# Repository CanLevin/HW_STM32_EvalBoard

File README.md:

# HW_STM32_EvalBoard
# HW Circuit and Layout for a simple Evaluation Board for a STM32F401
# wtih:
# SPI
# I2C
# UART
# USART# USB_HS-FS

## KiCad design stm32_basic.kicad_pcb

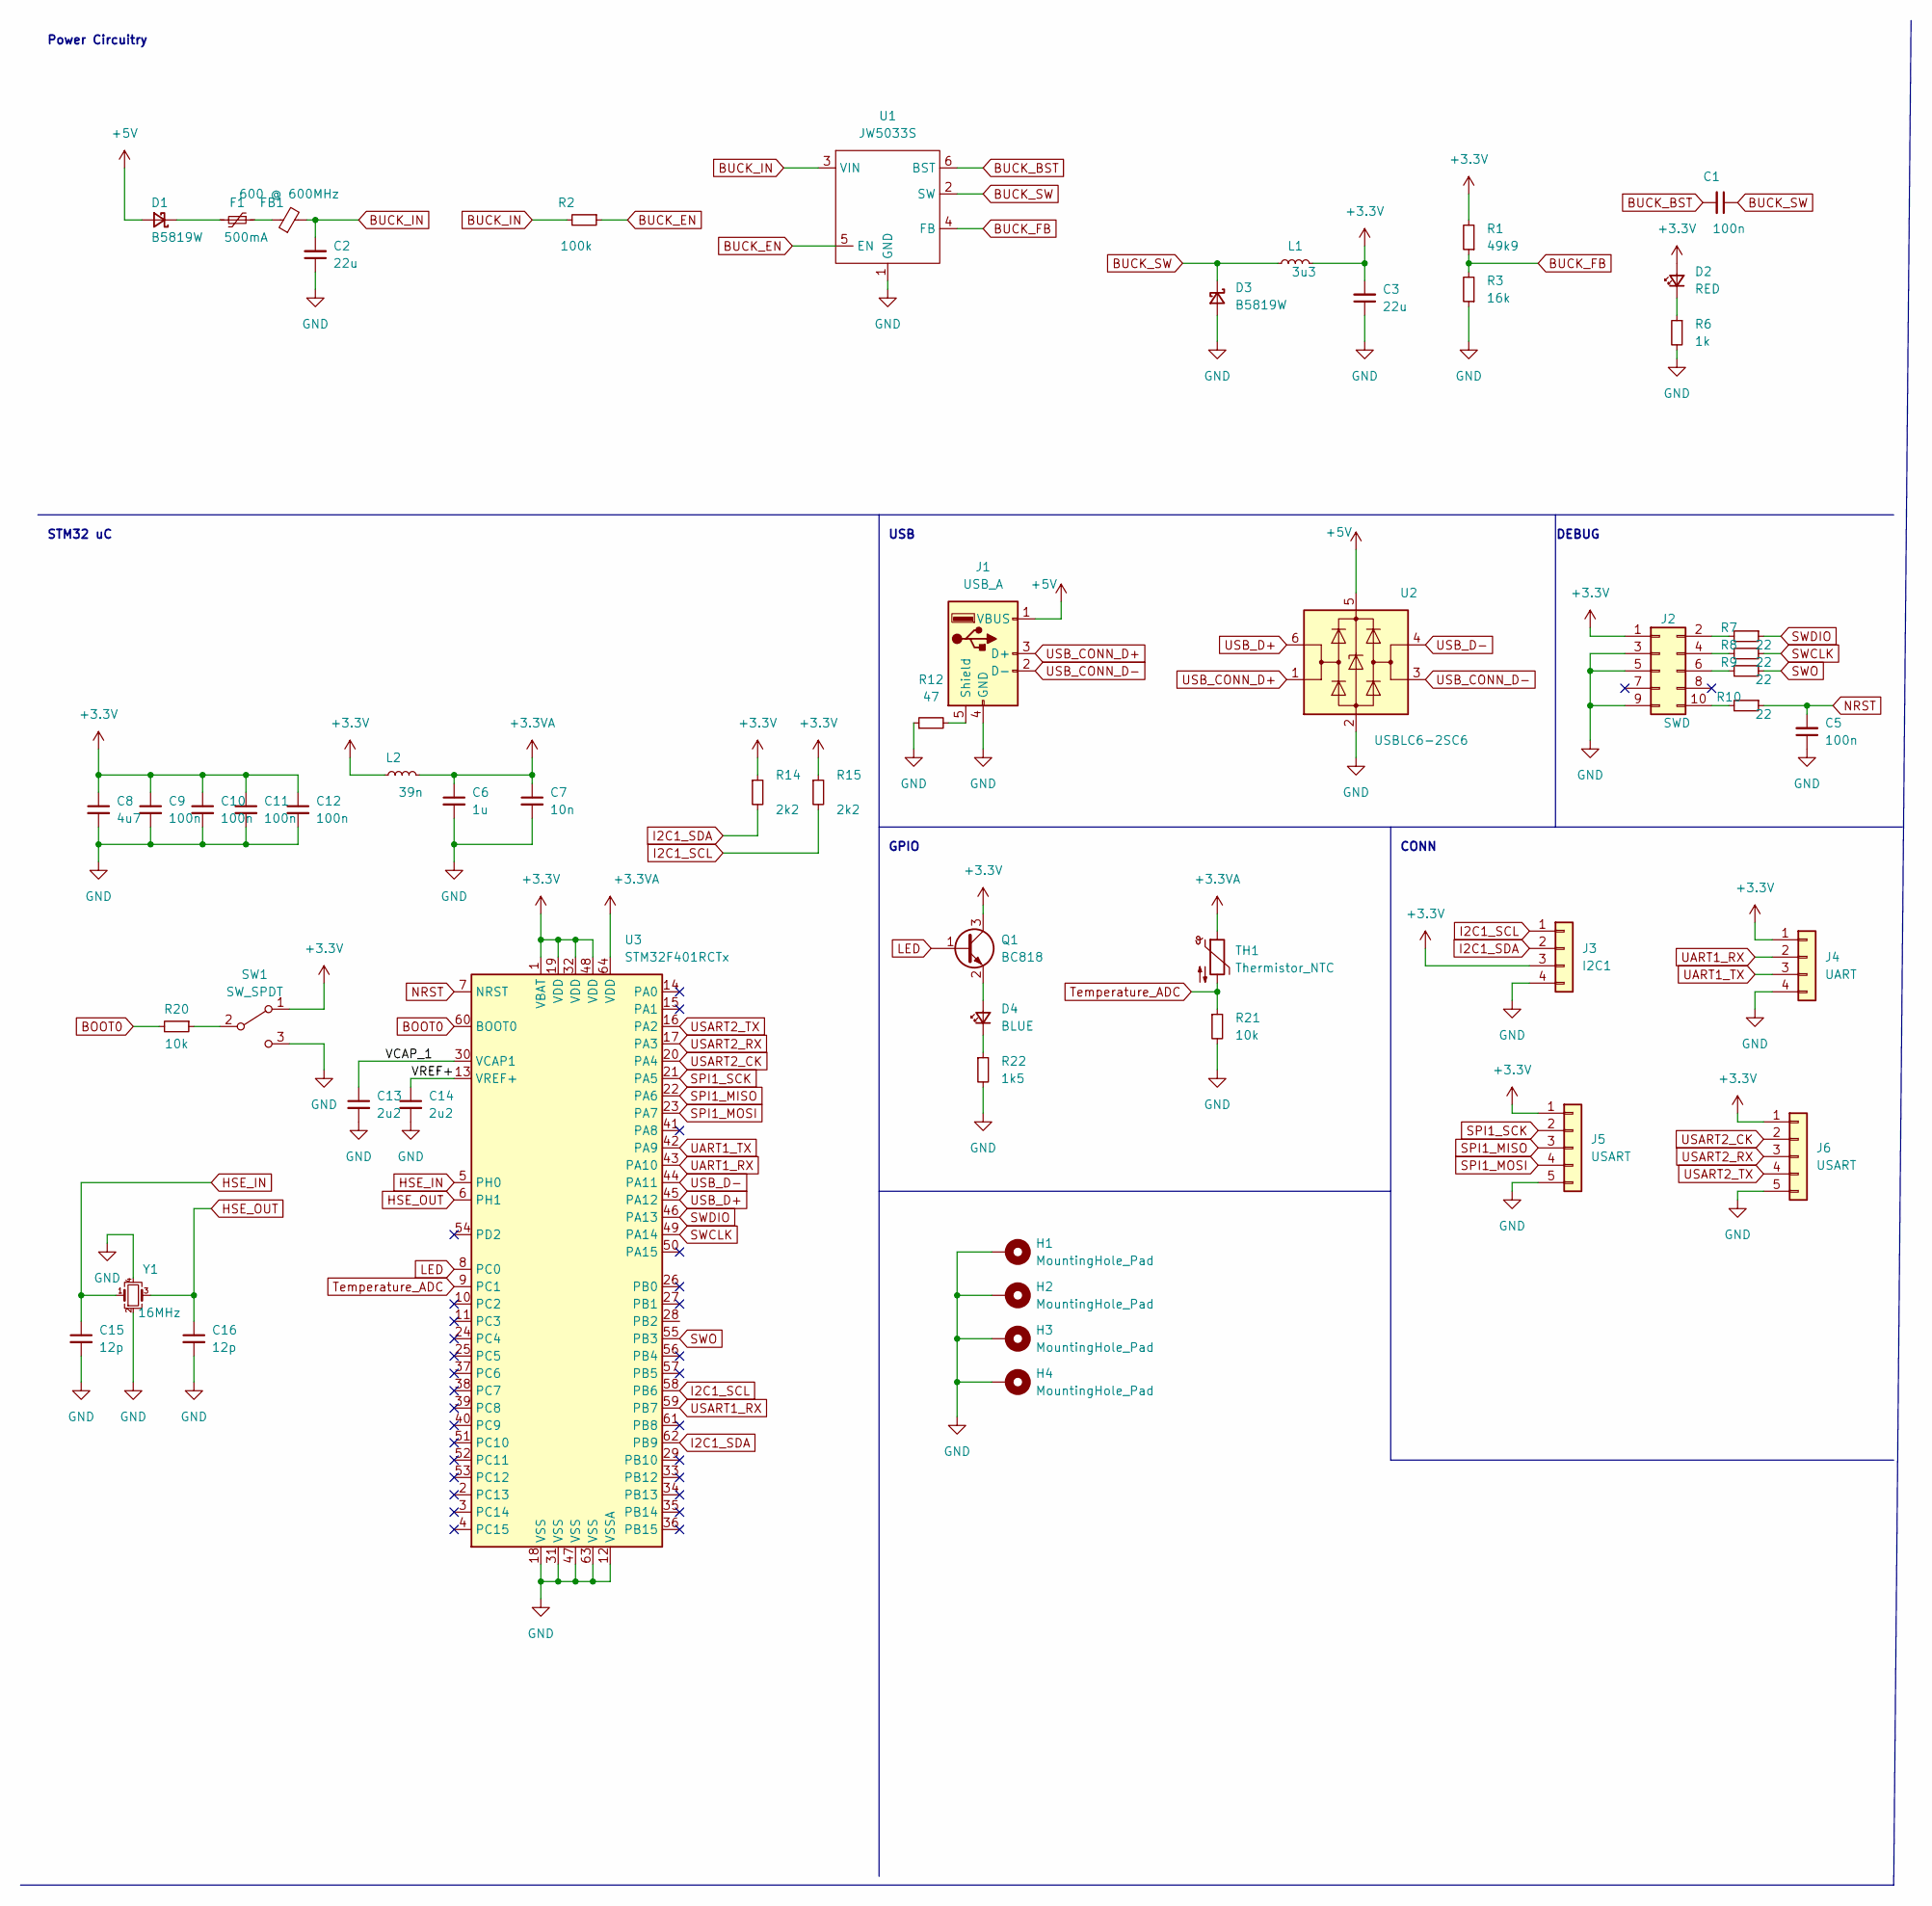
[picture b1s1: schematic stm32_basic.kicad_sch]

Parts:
C1: 100n; C_0402_1005Metric; LCSC Part # C15195
C2, C3: 22u; C_1206_3216Metric; LCSC Part # C12891
C5, C9, C10, C11, C12: 100n; C_0603_1608Metric; LCSC Part # C14663
C6: 1u; C_0402_1005Metric; LCSC Part # C52923
C7: 10n; C_0402_1005Metric; LCSC Part # C15195
C8: 4u7; C_0603_1608Metric; LCSC Part # C19666
C13, C14: 2u2; C_0402_1005Metric; LCSC Part # C12530
C15, C16: 12p; C_0402_1005Metric; LCSC Part # C1547
D1, D3: B5819W; D_SOD-123; LCSC Part # C64885
D2: RED; LED_0603_1608Metric; LCSC Part # C2286
D4: BLUE; LED_0603_1608Metric; LCSC Part # C72041
F1: 500mA; Fuse_1206_3216Metric; LCSC Part # C369159
FB1: 600 @ 600MHz; L_0805_2012Metric; LCSC Part # C1017
H1, H2, H3, H4: MountingHole_Pad; MountingHole_4.3mm_M4_Pad_Via
J1: USB_A; USB_A_CNCTech_1001-011-01101_Horizontal; LCSC Part # C319178
J2: SWD; PinSocket_2x05_P1.27mm_Vertical_SMD
J3: I2C1; PinHeader_1x04_P2.54mm_Vertical
J4: UART; PinHeader_1x04_P2.54mm_Vertical
J5, J6: USART; PinHeader_1x05_P2.54mm_Vertical
L1: 3u3; L_Sunlord_MWSA0518_5.4x5.2mm; LCSC Part # C325963
L2: 39n; L_0402_1005Metric; LCSC Part # C26443
Q1: BC818; SOT-23; LCSC Part # C154797
R1: 49k9; R_0603_1608Metric; LCSC Part # C25819
R2: 100k; R_0603_1608Metric; LCSC Part # C25803
R3: 16k; R_0603_1608Metric; LCSC Part # C22809
R6: 1k; R_0603_1608Metric; LCSC Part # C22190
R7, R8, R9, R10: 22; R_0603_1608Metric; LCSC Part # C23345
R12: 47; R_0603_1608Metric; LCSC Part # C23182
R14, R15: 2k2; R_0603_1608Metric; LCSC Part # C4190
R20: 10k; R_0402_1005Metric; LCSC Part # C25744
R21: 10k; R_0603_1608Metric; LCSC Part # C25804
R22: 1k5; R_0603_1608Metric; LCSC Part # C22843
SW1: SW_SPDT; SW_SPDT_PCM12; LCSC Part # C319019
TH1: Thermistor_NTC; R_0603_1608Metric; LCSC Part # C13564
U1: JW5033S; SOT-23-6
U2: USBLC6-2SC6; SOT-23-6; LCSC Part # C7519
U3: STM32F401RCTx; LQFP-64_10x10mm_P0.5mm; LCSC Part # C74524
Y1: 16MHz; Crystal_SMD_Abracon_ABM3B-4Pin_5.0x3.2mm; LCSC Part # C13738

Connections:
+3.3V: C3.2, C8.1, C9.1, C10.1, C11.1, C12.1, D2.2 (A), J2.1, J3.3, J4.1, J5.1, J6.1, L1.2, L2.1, Q1.3 (C), R1.2, R14.1, R15.1, SW1.1 (A), U3.1 (VBAT), U3.19 (VDD), U3.32 (VDD), U3.48 (VDD); also elsewhere on the board
+3.3VA: C6.1, C7.1, L2.2, TH1.1, U3.64 (VDD)
+5V: D1.2 (A), J1.1 (VBUS), U2.5 (VBUS)
/VCAP_1: C13.1, U3.30 (VCAP1)
/VREF+: C14.1, U3.13 (VREF+)
BOOT0: R20.2, U3.60 (BOOT0)
BUCK_BST: C1.2, U1.6 (BST)
BUCK_EN: R2.1, U1.5 (EN)
BUCK_FB: R1.1, R3.2, U1.4 (FB)
BUCK_IN: C2.2, FB1.2, R2.2, U1.3 (VIN)
BUCK_SW: C1.1, D3.1 (K), L1.1, U1.2 (SW)
GND: C2.1, C3.1, C5.1, C6.2, C7.2, C8.2, C9.2, C10.2, C11.2, C12.2, C13.2, C14.2, C15.2, C16.2, D3.2 (A), H1.1, H2.1, H3.1, H4.1, J1.4 (GND), J2.3, J2.5, J2.9, J3.4, J4.4, J5.5, J6.5, R3.1, R6.2, R12.1, R21.2, R22.2, SW1.3 (C), U1.1 (GND), U2.2 (GND), U3.12 (VSSA), U3.18 (VSS), U3.31 (VSS), U3.47 (VSS), U3.63 (VSS), Y1.2, Y1.4; also elsewhere on the board
HSE_IN: C15.1, U3.5 (PH0), Y1.1
HSE_OUT: C16.1, U3.6 (PH1), Y1.3
I2C1_SCL: J3.1, R15.2, U3.58 (PB6)
I2C1_SDA: J3.2, R14.2, U3.62 (PB9)
LED: Q1.1 (B), U3.8 (PC0)
NRST: C5.2, R10.1, U3.7 (NRST)
unnamed: D1.1 (K), F1.2
unnamed: D2.1 (K), R6.1
unnamed: D4.1 (K), R22.1
unnamed: D4.2 (A), Q1.2 (E)
unnamed: F1.1, FB1.1
unnamed: J1.5 (Shield), R12.2
unnamed: J2.2, R7.2
unnamed: J2.4, R8.2
unnamed: J2.6, R9.2
unnamed: J2.10, R10.2
unnamed: R20.1, SW1.2 (B)
SPI1_MISO: J5.3, U3.22 (PA6)
SPI1_MOSI: J5.4, U3.23 (PA7)
SPI1_SCK: J5.2, U3.21 (PA5)
SWCLK: R8.1, U3.49 (PA14)
SWDIO: R7.1, U3.46 (PA13)
SWO: R9.1, U3.55 (PB3)
Temperature_ADC: R21.1, TH1.2, U3.9 (PC1)
UART1_RX: J4.2, U3.43 (PA10)
UART1_TX: J4.3, U3.42 (PA9)
USART1_RX: U3.59 (PB7)
USART2_CK: J6.2, U3.20 (PA4)
USART2_RX: J6.3, U3.17 (PA3)
USART2_TX: J6.4, U3.16 (PA2)
USB_CONN_D+: J1.3 (D+), U2.1 (I/O1)
USB_CONN_D-: J1.2 (D-), U2.3 (I/O2)
USB_D+: U2.6 (I/O1), U3.45 (PA12)
USB_D-: U2.4 (I/O2), U3.44 (PA11)

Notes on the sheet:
GPIO
STM32 uC
Power Circuitry
USB
DEBUG
CONN

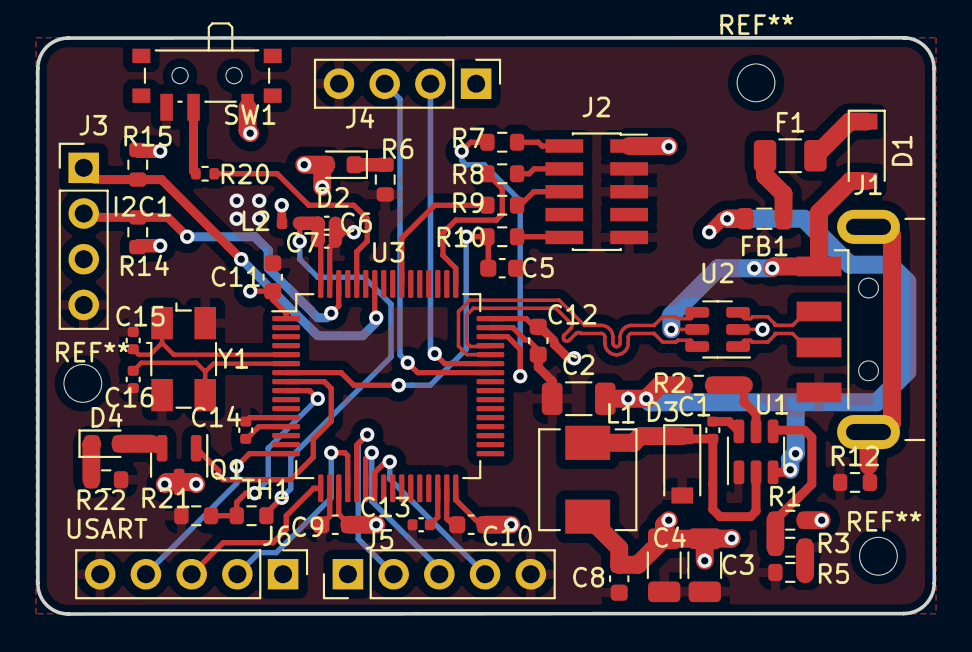
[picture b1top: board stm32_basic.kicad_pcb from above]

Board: 4 copper layers, 49.8 x 32.0 mm, 52 parts (0 on the bottom side), 45 nets.

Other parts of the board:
C4: 10u; C_1206_3216Metric
R5: 270; R_0603_1608Metric

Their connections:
+3.3V: C4.2; also elsewhere on the board
GND: C4.1, R5.1; also elsewhere on the board

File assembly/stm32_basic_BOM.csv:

Comment,Designator,Footprint,LCSC Part #
"100n","C1","Capacitor_SMD:C_0402_1005Metric","C15195"
"2u2","C13,C14","Capacitor_SMD:C_0402_1005Metric","C12530"
"12p","C15,C16","Capacitor_SMD:C_0402_1005Metric","C1547"
"22u","C2,C3","Capacitor_SMD:C_1206_3216Metric","C12891"
"100n","C5,C9,C10,C11,C12","Capacitor_SMD:C_0603_1608Metric","C14663"
"1u","C6","Capacitor_SMD:C_0402_1005Metric","C52923"
"10n","C7","Capacitor_SMD:C_0402_1005Metric","C15195"
"4u7","C8","Capacitor_SMD:C_0603_1608Metric","C19666"
"B5819W","D1,D3","Diode_SMD:D_SOD-123","C64885"
"RED","D2","LED_SMD:LED_0603_1608Metric","C2286"
"BLUE","D4","LED_SMD:LED_0603_1608Metric","C72041"
"500mA","F1","Fuse:Fuse_1206_3216Metric","C369159"
"600 @ 600MHz","FB1","Inductor_SMD:L_0805_2012Metric","C1017"
"MountingHole_Pad","H1,H2,H3,H4","MountingHole:MountingHole_4.3mm_M4_Pad_Via",""
"USB_A","J1","Connector_USB:USB_A_CNCTech_1001-011-01101_Horizontal","C319178 "
"SWD","J2","Connector_PinSocket_1.27mm:PinSocket_2x05_P1.27mm_Vertical_SMD",""
"I2C1","J3","Connector_PinHeader_2.54mm:PinHeader_1x04_P2.54mm_Vertical",""
"UART","J4","Connector_PinHeader_2.54mm:PinHeader_1x04_P2.54mm_Vertical",""
"USART","J5,J6","Connector_PinHeader_2.54mm:PinHeader_1x05_P2.54mm_Vertical",""
"3u3","L1","Inductor_SMD:L_Sunlord_MWSA0518_5.4x5.2mm","C325963"
"39n","L2","Inductor_SMD:L_0402_1005Metric","C26443"
"BC818","Q1","Package_TO_SOT_SMD:SOT-23","C154797"
"49k9","R1","Resistor_SMD:R_0603_1608Metric","C25819"
"47","R12","Resistor_SMD:R_0603_1608Metric","C23182"
"2k2","R14,R15","Resistor_SMD:R_0603_1608Metric","C4190"
"100k","R2","Resistor_SMD:R_0603_1608Metric","C25803"
"10k","R20","Resistor_SMD:R_0402_1005Metric","C25744"
"10k","R21","Resistor_SMD:R_0603_1608Metric","C25804"
"1k5","R22","Resistor_SMD:R_0603_1608Metric","C22843"
"16k","R3","Resistor_SMD:R_0603_1608Metric","C22809"
"1k","R6","Resistor_SMD:R_0603_1608Metric","C22190"
"22","R7,R8,R9,R10","Resistor_SMD:R_0603_1608Metric","C23345"
"SW_SPDT","SW1","Button_Switch_SMD:SW_SPDT_PCM12","C319019"
"Thermistor_NTC","TH1","Resistor_SMD:R_0603_1608Metric","C13564"
"JW5033S","U1","Package_TO_SOT_SMD:SOT-23-6",""
"USBLC6-2SC6","U2","Package_TO_SOT_SMD:SOT-23-6","C7519"
"STM32F401RCTx","U3","Package_QFP:LQFP-64_10x10mm_P0.5mm","C74524"
"16MHz","Y1","Crystal:Crystal_SMD_Abracon_ABM3B-4Pin_5.0x3.2mm","C13738"

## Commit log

2023-03-06 Init
